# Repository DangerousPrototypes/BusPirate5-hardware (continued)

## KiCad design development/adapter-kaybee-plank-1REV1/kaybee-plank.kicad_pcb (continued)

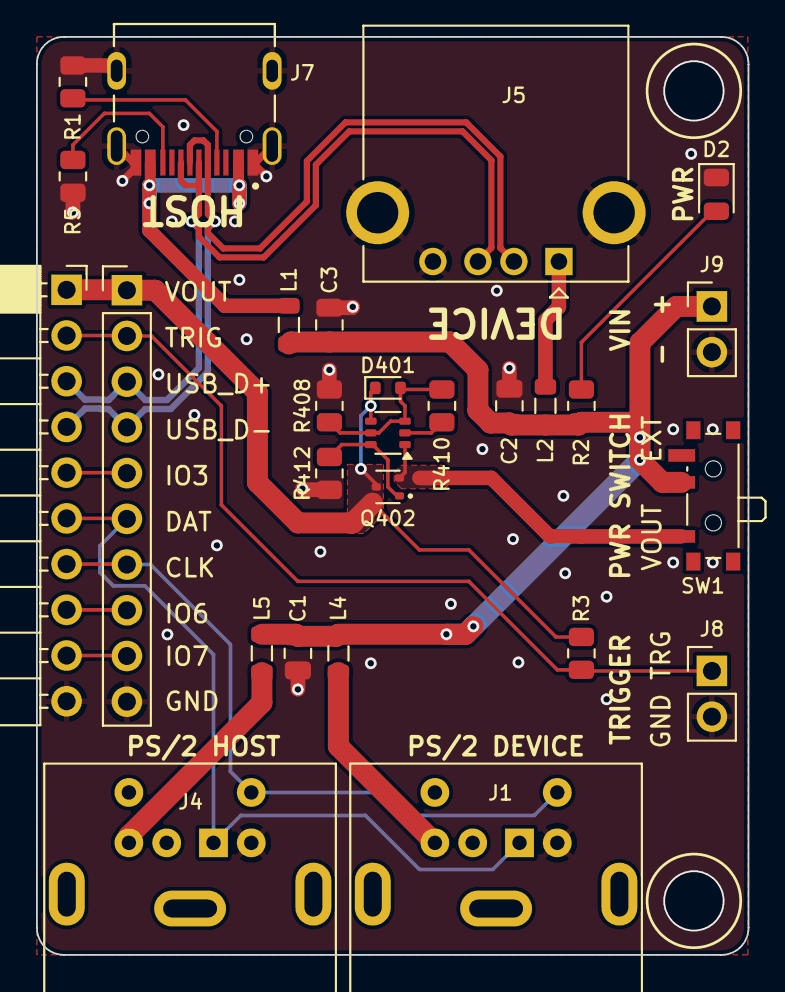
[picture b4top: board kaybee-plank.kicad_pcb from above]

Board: 2 copper layers, 39.5 x 51.0 mm, 27 parts (0 on the bottom side), 22 nets.

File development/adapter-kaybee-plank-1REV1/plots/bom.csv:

Item,Qty,Reference(s),Value,Footprint,szlcsc_partnum
1,3,"C1, C2, C3",47uF/CL21A226MAYNNNE,Capacitor_SMD:C_0805_2012Metric,C602037
2,1,D2,LED,LED_SMD:LED_0805_2012Metric,
3,1,D401,1N4148WT,Diode_SMD:D_SOD-523,C2828426
4,2,"J1, J4",Mini-DIN-6,connector-mini-din-6:Connector_Mini-DIN_Female_6Pin_2rows,C77848
5,1,J2,Conn_01x10,Connector_PinSocket_2.54mm:PinSocket_1x10_P2.54mm_Horizontal,
6,1,J5,USB_A,Connector_USB:USB_A_CONNFLY_DS1095-WNR0,C456018
7,1,J7,TYPE-C-31-M-12,TYPE-C-31-M-12:HRO_TYPE-C-31-M-12,C2858270
8,2,"J8, J9",Conn_01x02_Pin,Connector_PinHeader_2.54mm:PinHeader_1x02_P2.54mm_Vertical,C2905434
9,4,"L1, L2, L4, L5",CBW201209U300T,Inductor_SMD:L_0805_2012Metric,C139190
10,1,Q401,BCM857BS-7-F,Package_TO_SOT_SMD:SOT-363_SC-70-6,C105896
11,1,Q402,BC2301T 2.8A,Package_TO_SOT_SMD:SOT-523,C21714127
12,2,"R1, R5",5.1K,Resistor_SMD:R_0805_2012Metric,C27834
13,2,"R2, R3",2K,Resistor_SMD:R_0805_2012Metric,C2907315
14,1,R408,68K,Resistor_SMD:R_0805_2012Metric,C17801
15,1,R410,10K,Resistor_SMD:R_0805_2012Metric,C17414
16,1,R412,100K,Resistor_SMD:R_0805_2012Metric,C149504
17,1,SW1,SW_SPDT,Button_Switch_SMD:SW_SPDT_PCM12,C431540

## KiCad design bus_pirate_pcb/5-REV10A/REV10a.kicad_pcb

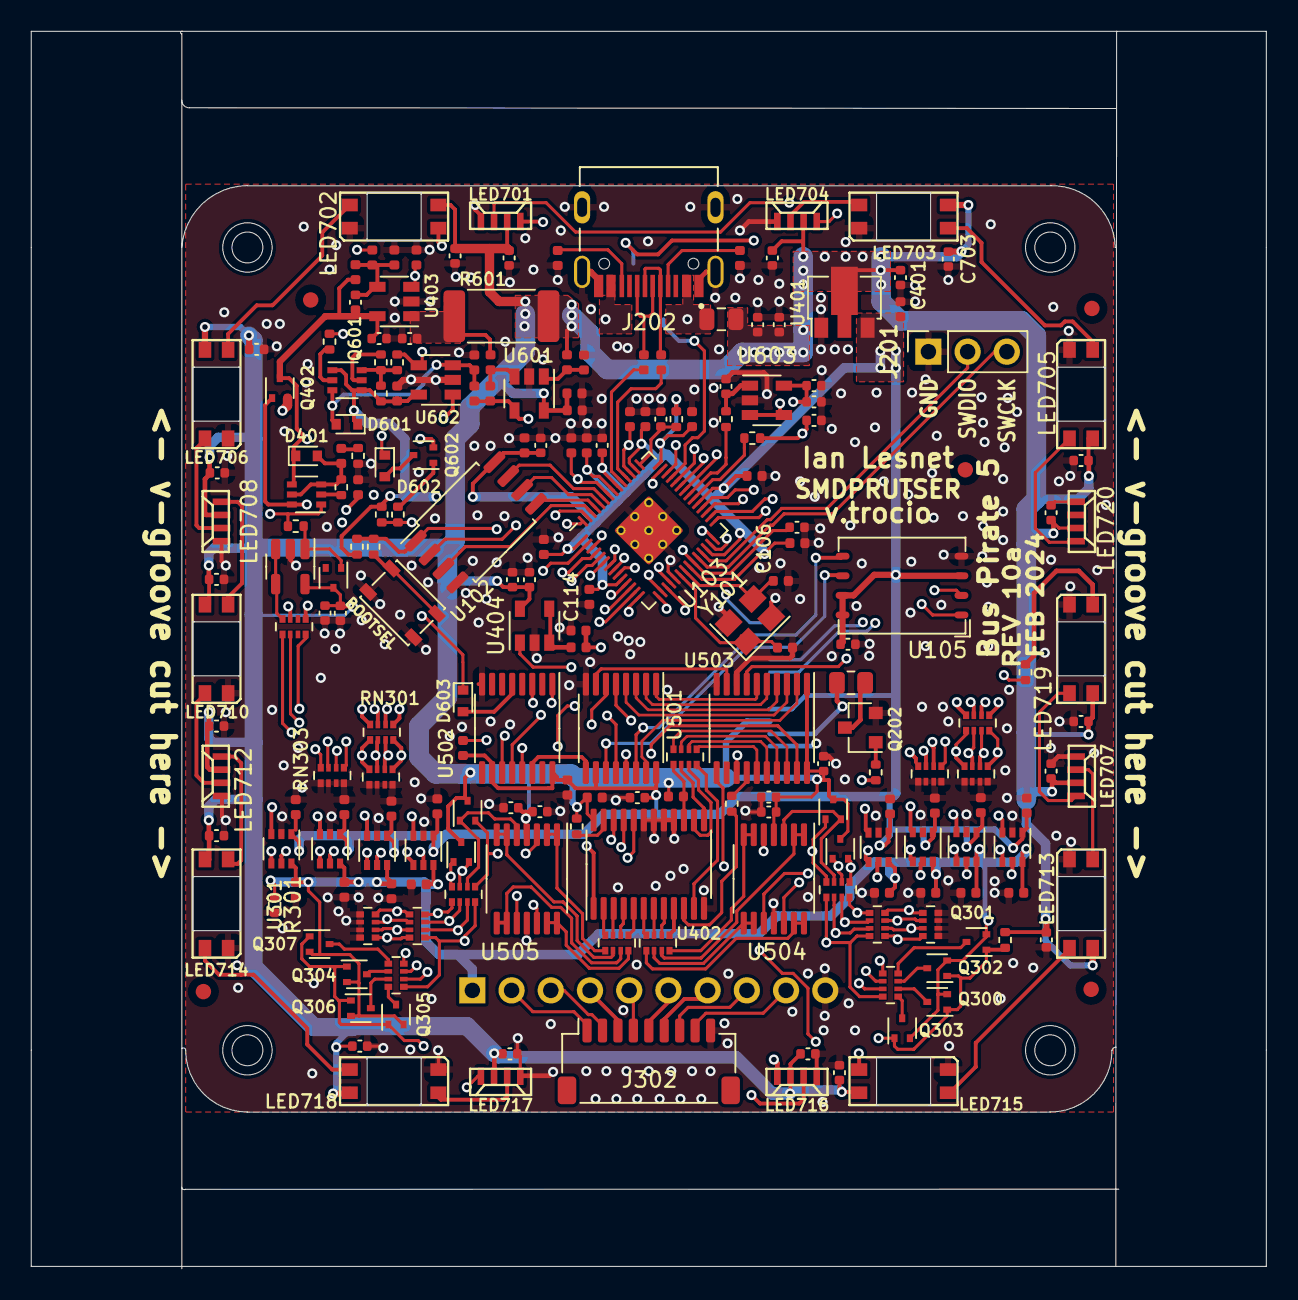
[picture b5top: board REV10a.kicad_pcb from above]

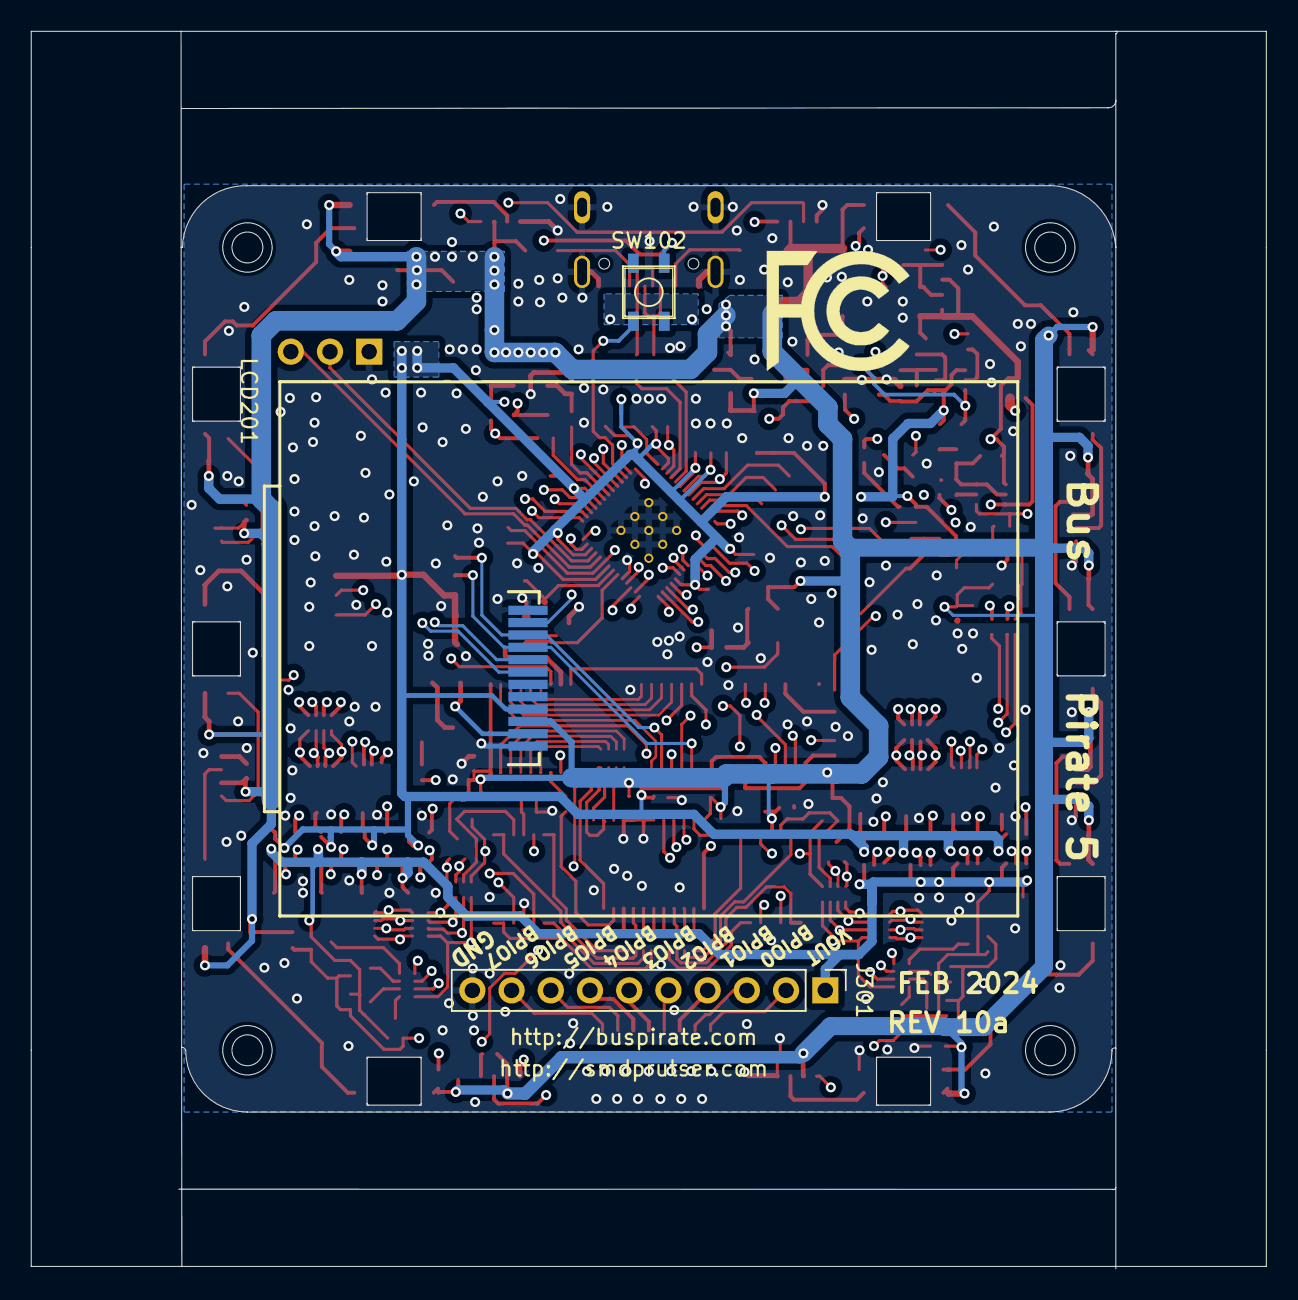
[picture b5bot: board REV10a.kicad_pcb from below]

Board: 4 copper layers, 80.0 x 80.0 mm, 220 parts (4 on the bottom side), 183 nets.

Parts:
C103, C110, C111, C112, C113, C114, C115, C116, C117, C118, C121, C301, C302, C303, C304, C305, C306, C307, C308, C309, C310, C311, C312, C313, C314, C315, C316, C403, C406, C414, C415, C416, C501, C502, C503, C506, C508, C510, C602, C605, C701, C702, C703, C704, C705, C706, C707, C708, C710, C712, C713, C714, C715, C716, C717, C718, C719, C720: 0.1uF; C_0402_1005Metric
C104, C107, C108, C109, C405, C413, C504, C507, C509, C601: 2.2uF; C_0402_1005Metric
C105, C106: 15pF; C_0402_1005Metric
C201, C202, C401, C402, C404, C407: 4.7uF; C_0402_1005Metric
C408: 120pF; C_0402_1005Metric
C603: DNF; C_0402_1005Metric
D401, D601, D602, D603: 1N4148WT; D_SOD-523
D500, D501, D502, D503, D504: BAS40T-05; SOT-523
FID1, FID2, FID3, FID4, FID5: Fiducial; Fiducial_1mm_Mask2mm
H1, H2, H3, H4: MountingHole; MountingHole_3.2mm_M3
J201: Conn_01x03; PinSocket_1x03_P2.54mm_Vertical
J202: TYPE-C-31-M-12; HRO_TYPE-C-31-M-12
J301: Conn_01x10; PinHeader_1x10_P2.54mm_Vertical
J302: Conn_01x09; JST_SH_SM09B-SRSS-TB_1x09-1MP_P1.00mm_Horizontal
L201: 1.5A; L_0805_2012Metric
LCD201: TFT_20_QT200H1201
LED701, LED704, LED707, LED708, LED712, LED716, LED717, LED720: SK6812-side-a_b
LED702, LED703, LED705, LED706, LED710, LED713, LED714, LED715, LED718, LED719: SK6812-mini-e
Q202: MMBT7002K; SOT-23
Q300, Q301, Q302, Q303, Q304, Q305, Q306, Q307, Q402, Q602: SI2301; SOT-523
Q401: BCM857; SOT-363_SC-70-6
Q601: MMDT3906; SOT-363_SC-70-6
R101, R502, R602, R603: 1K; R_0402_1005Metric
R102: DNF; R_0402_1005Metric
R103, R208, R608, R612: 200R; R_0402_1005Metric
R201, R204: 5.1K; R_0402_1005Metric
R202, R203: 22R; R_0402_1005Metric
R209: 33R; R_0805_2012Metric
R301, R313, R402, R406, R407, R410, R414, R415, R501, R606, R609, R610, R611, R613: 10K; R_0402_1005Metric
R316, R320: 510R; R_0402_1005Metric
R319, R401, R412: 100K; R_0402_1005Metric
R403: 102K; R_0402_1005Metric
R404: 133K; R_0402_1005Metric
R405, R408, R409, R604, R605: 33K; R_0402_1005Metric
R601: 0R2; R_2512_6332Metric_Pad1.40x3.35mm_HandSolder
RN301, RN305, RN306, RN309: 330R; R_Array_Convex_4x0402
RN302, RN304, RN307, RN310: 1M; R_Array_Convex_4x0402
RN303, RN308, RN317, RN318: 100K; R_Array_Convex_4x0402
RN311, RN312: 10K; R_Array_Convex_4x0402
RN315, RN400, RN401, RN402: 510R; R_Array_Convex_4x0402
SW101: SW_SPST; SW_SPST_PTS810
SW102: 4P_button_sw; GT-TC026X-HXXX-LX
U102: W25Q128JVSIQ; SOP-8_5.28x5.23mm_P1.27mm
U103: RP2040; RP2040-QFN-56
U105: MT29F1G01ABAFDWB; U-PDFN-8
U301, U302, U303, U304, U305, U306, U307, U308: AiP74LVC1T45GC363.TR; SOT-363_SC-70-6
U401: ME6211A33PG-N; SOT-89-3
U402: CD4067; TSSOP-24_4.4x7.8mm_P0.65mm
U403: AP2127; SOT-23-5
U404, U506, U603: LMV321; SOT-23-5
U501, U502: AIP74HC595TA; TSSOP-16_4.4x5mm_P0.65mm
U503: AIP74HCT245TA; TSSOP-20_4.4x6.5mm_P0.65mm
U504, U505: LMV324; TSSOP-14_4.4x5mm_P0.65mm
U601: LMV321A; SOT-23-5
U602: LMV331; SOT-23-5
Y101: 12Mhz; Crystal_SMD_3225-4Pin_3.2x2.5mm
logo1: fcc_logo; logo_fcc

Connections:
+1V1: C107.1, C117.1, C118.1, U103.23 (DVDD), U103.45 (VREG_VOUT), U103.50 (DVDD)
+3V3: C103.1, C104.1, C108.2, C110.1, C111.1, C112.1, C113.1, C114.1, C115.1, C116.1, C121.1, C301.2, C302.2, C303.2, C307.2, C308.2, C309.2, C313.2, C314.2, C402.1, C413.1, C414.2, C501.2, C502.2, C605.1, D601.1 (K), LCD201.4 (VCC), Q601.1 (E1), Q601.4 (E2), R102.1, R103.1, R501.1, R609.1, R613.1, SW102.4, U102.8 (VCC), U103.1 (IOVDD), U103.10 (IOVDD), U103.22 (IOVDD), U103.26 (RUN), U103.33 (IOVDD), U103.42 (IOVDD), U103.44 (VREG_IN), U103.48 (USB_VDD), U103.49 (IOVDD), U105.3 (WP/IO2), U105.7 (HOLD/IO3), U105.8 (VCC), U301.1 (VCCA), U302.1 (VCCA), U303.1 (VCCA), U304.1 (VCCA), U305.1 (VCCA), U306.1 (VCCA), U307.1 (VCCA), U308.1 (VCCA), U401.3 (VOUT), U501.10 (~SRCLR), U501.16 (VCC), U502.10 (~SRCLR), U502.16 (VCC), U602.5 (V+), U603.5 (V+)
+VUSB: C201.2, C202.2, C401.1, C403.2, C405.2, C406.1, C503.2, C504.2, C506.1, C507.2, C508.2, C509.2, C510.2, C601.1, C602.2, C701.2, C702.2, C703.2, C704.2, C705.2, C706.2, C707.2, C708.2, C710.2, C712.2, C713.2, C714.2, C715.2, C716.2, C717.2, C718.2, C719.2, C720.2, D500.3, D501.3, D502.3, D503.3, D504.3, L201.1, LCD201.3 (LED-A), LED701.3 (VDD), LED702.1 (VDD), LED703.1 (VDD), LED704.3 (VDD), LED705.1 (VDD), LED706.1 (VDD), LED707.3 (VDD), LED708.3 (VDD), LED710.1 (VDD), LED712.3 (VDD), LED713.1 (VDD), LED714.1 (VDD), LED715.1 (VDD), LED716.3 (VDD), LED717.3 (VDD), LED718.1 (VDD), LED719.1 (VDD), LED720.3 (VDD), R313.2, R320.2, R402.1, R601.1, R602.2, U401.2 (VIN), U402.24 (VCC), U404.5 (V+), U503.1 (A->B), U503.20 (VCC), U504.4 (V+), U505.4 (V+), U506.5 (V+), U601.5 (V+)
AMUX_EN: R402.2, RN315.1 (R1.1), U402.15 (~E)
AMUX_OUT: R406.2, R407.2, U103.40 (GPIO28_ADC2)
AMUX_S0: R316.1, U402.10 (S0)
AMUX_S1: RN315.4 (R1.1), U402.11 (S1)
AMUX_S2: RN315.3 (R1.1), U402.14 (S2)
AMUX_S3: RN315.2 (R1.1), U402.13 (S3)
BPIO0: J301.2, J302.1, RN305.1 (R1.1), RN312.1 (R1.1), RN318.8 (R1.8)
BPIO1: J301.3, J302.2, RN305.2 (R1.1), RN312.2 (R1.1), RN318.7 (R1.8)
BPIO2: J301.4, J302.3, RN305.3 (R1.1), RN312.3 (R1.1), RN318.6 (R1.8)
BPIO3: J301.5, J302.4, RN305.4 (R1.1), RN312.4 (R1.1), RN318.5 (R1.8)
BPIO4: J301.6, J302.5, RN309.1 (R1.1), RN311.1 (R1.1), RN317.8 (R1.8)
BPIO5: J301.7, J302.6, RN309.2 (R1.1), RN311.2 (R1.1), RN317.7 (R1.8)
BPIO6: J301.8, J302.7, RN309.3 (R1.1), RN311.3 (R1.1), RN317.6 (R1.8)
BPIO7: J301.9, J302.8, RN309.4 (R1.1), RN311.4 (R1.1), RN317.5 (R1.8)
BUFDIR0: RN303.8 (R1.8), U103.2 (GPIO0), U301.5 (DIR)
BUFDIR1: RN303.7 (R1.8), U103.3 (GPIO1), U302.5 (DIR)
BUFDIR2: RN303.6 (R1.8), U103.4 (GPIO2), U303.5 (DIR)
BUFDIR3: RN303.5 (R1.8), U103.5 (GPIO3), U304.5 (DIR)
BUFDIR4: RN308.8 (R1.8), U103.6 (GPIO4), U305.5 (DIR)
BUFDIR5: RN308.7 (R1.8), U103.7 (GPIO5), U306.5 (DIR)
BUFDIR6: RN308.6 (R1.8), U103.8 (GPIO6), U307.5 (DIR)
BUFDIR7: RN308.5 (R1.8), U103.9 (GPIO7), U308.5 (DIR)
BUFIO0: RN301.8 (R1.8), U103.11 (GPIO8)
BUFIO1: RN301.7 (R1.8), U103.12 (GPIO9)
BUFIO2: RN301.6 (R1.8), U103.13 (GPIO10)
BUFIO3: RN301.5 (R1.8), U103.14 (GPIO11)
BUFIO4: RN306.8 (R1.8), U103.15 (GPIO12)
BUFIO5: RN306.7 (R1.8), U103.16 (GPIO13)
BUFIO6: RN306.6 (R1.8), U103.17 (GPIO14)
BUFIO7: RN306.5 (R1.8), U103.18 (GPIO15)
BUTTONS: SW102.1, U103.39 (GPIO27_ADC1)
CURRENT_ADJ_MCU: R415.2, U103.34 (GPIO22)
CURRENT_DETECT: Q602.2 (S), R610.2, RN402.5 (R1.8), U602.4
CURRENT_EN: R612.2, R613.2, U502.1 (QB)
CURRENT_EN_OVERRIDE: D603.2 (A), U502.5 (QF)
CURRENT_RESET: R611.1, U502.3 (QD)
CURRENT_SENSE: R605.1, R606.2, U103.41 (GPIO29_ADC3), U601.4
DISPLAY_BACKLIGHT: R208.1, U501.5 (QF)
DISPLAY_CS: LCD201.8 (CS), U103.37 (GPIO25)
DISPLAY_DP: LCD201.7 (WR/SPI_A0), U103.36 (GPIO24)
DISPLAY_LED-K: LCD201.2 (LED-K), R209.2
DISPLAY_RESET: LCD201.11 (RESET), U501.6 (QG)
GND: C103.2, C104.2, C105.2, C106.2, C107.2, C108.1, C109.2, C110.2, C111.2, C112.2, C113.2, C114.2, C115.2, C116.2, C117.2, C118.2, C121.2, C201.1, C202.1, C301.1, C302.1, C303.1, C304.2, C305.2, C306.2, C307.1, C308.1, C309.1, C310.2, C311.2, C312.2, C313.1, C314.1, C315.2, C316.2, C401.2, C402.2, C403.1, C404.2, C405.1, C406.2, C407.2, C413.2, C414.1, C415.1, C416.1, C501.1, C502.1, C503.1, C504.1, C506.2, C507.1, C508.1, C509.1, C510.1, C601.2, C602.1, C603.1, C605.2, C701.1, C702.1, C703.1, C704.1, C705.1, C706.1, C707.1, C708.1, C710.1, C712.1, C713.1, C714.1, C715.1, C716.1, C717.1, C718.1, C719.1, C720.1, J201.1, J202.A1B12 (GND), J202.B1A12 (GND), J202.S1 (SHIELD), J202.S2 (SHIELD), J202.S3 (SHIELD), J202.S4 (SHIELD), J301.10, J302.9, LCD201.1 (GND), LCD201.5 (GND), LCD201.6 (GND), LCD201.12 (GND), LED701.1 (VSS), LED702.3 (VSS), LED703.3 (VSS), LED704.1 (VSS), LED705.3 (VSS), LED706.3 (VSS), LED707.1 (VSS), LED708.1 (VSS), LED710.3 (VSS), LED712.1 (VSS), LED713.3 (VSS), LED714.3 (VSS), LED715.3 (VSS), LED716.1 (VSS), LED717.1 (VSS), LED718.3 (VSS), LED719.3 (VSS), LED720.1 (VSS), Q202.2 (S), R201.1, R204.1, R301.2, R401.2, R405.2, R407.1, R409.2, R412.2, R604.1, RN302.1 (R1.1), RN302.2 (R1.1), RN302.3 (R1.1), RN302.4 (R1.1), RN303.1 (R1.1), RN303.2 (R1.1), RN303.3 (R1.1), RN303.4 (R1.1), RN304.5 (R1.8), RN304.6 (R1.8), RN304.7 (R1.8), RN304.8 (R1.8), RN307.1 (R1.1), RN307.2 (R1.1), RN307.3 (R1.1), RN307.4 (R1.1), RN308.1 (R1.1), RN308.2 (R1.1), RN308.3 (R1.1), RN308.4 (R1.1), RN310.5 (R1.8), RN310.6 (R1.8), RN310.7 (R1.8), RN310.8 (R1.8), SW101.2 (B), U102.4 (VSS), U103.19 (TESTEN), U103.57 (GND), U105.4 (VSS), U301.2 (GND), U302.2 (GND), U303.2 (GND), U304.2 (GND), U305.2 (GND), U306.2 (GND), U307.2 (GND), U308.2 (GND), U401.1 (GND), U402.12 (GND), U402.16 (I15), U402.17 (I14), U402.18 (I13), U402.19 (I12), U403.2 (GND), U404.2 (V-), U501.8 (GND), U502.8 (GND), U503.8 (A6), U503.10 (GND), U504.11 (V-), U505.11 (V-), U506.2 (V-), U601.2 (V-), U602.2 (V-), U603.2 (V-), Y101.2, Y101.4
LEDS_CDO: R502.1, U503.13 (B5)
MUX_BPIO0: RN401.5 (R1.8), U505.1, U505.2 (-)
MUX_BPIO1: RN401.6 (R1.8), U505.6 (-), U505.7
MUX_BPIO2: RN401.7 (R1.8), U505.8, U505.9 (-)
MUX_BPIO3: RN401.8 (R1.8), U505.13 (-), U505.14
MUX_BPIO4: RN400.5 (R1.8), U504.13 (-), U504.14
MUX_BPIO5: RN400.6 (R1.8), U504.8, U504.9 (-)
MUX_BPIO6: RN400.7 (R1.8), U504.1, U504.2 (-)
MUX_BPIO7: RN400.8 (R1.8), U504.6 (-), U504.7
MUX_VREF_VOUT: RN402.8 (R1.8), U506.3 (-), U506.4
unnamed: D401.2 (A), Q401.3 (C2), Q401.5 (B2), R408.2, R410.2
unnamed: C603.2, D601.2 (A), Q601.3 (C2), R606.1, U602.3 (-)
unnamed: D602.2 (A), Q602.3 (D)
unnamed: J202.A5 (CC1), R201.2
unnamed: J202.B5 (CC2), R204.2
unnamed: J202.A4B9 (VBUS), J202.B4A9 (VBUS), L201.2
unnamed: LED701.4 (DI), LED702.2 (DO)
unnamed: LED701.2 (DO), LED704.4 (DI)
unnamed: LED702.4 (DI), LED706.2 (DO)
unnamed: LED703.4 (DI), LED704.2 (DO)
unnamed: LED703.2 (DO), LED705.4 (DI)
unnamed: LED705.2 (DO), LED720.4 (DI)
unnamed: LED706.4 (DI), LED708.2 (DO)
unnamed: LED707.4 (DI), LED719.2 (DO)
unnamed: LED707.2 (DO), LED713.4 (DI)
unnamed: LED708.4 (DI), LED710.2 (DO)
unnamed: LED710.4 (DI), LED712.2 (DO)
unnamed: LED712.4 (DI), LED714.2 (DO)
unnamed: LED713.2 (DO), LED715.4 (DI)
unnamed: LED714.4 (DI), LED718.2 (DO)
unnamed: LED715.2 (DO), LED716.4 (DI)
unnamed: LED716.2 (DO), LED717.4 (DI)
unnamed: LED717.2 (DO), LED718.4 (DI)
unnamed: LED719.4 (DI), R502.2
unnamed: Q202.3 (D), R209.1
unnamed: Q202.1 (G), R208.2
unnamed: Q300.3 (D), RN311.6 (R1.8)
unnamed: Q301.3 (D), RN311.8 (R1.8)
unnamed: Q302.3 (D), RN311.7 (R1.8)
unnamed: Q303.3 (D), RN311.5 (R1.8)
unnamed: Q304.3 (D), RN312.6 (R1.8)
unnamed: Q305.3 (D), RN312.8 (R1.8)
unnamed: Q306.3 (D), RN312.7 (R1.8)
unnamed: Q307.3 (D), RN312.5 (R1.8)
unnamed: Q401.2 (B1), R410.1
unnamed: Q401.6 (C1), Q402.1 (G), R412.1
unnamed: Q601.2 (B1), R611.2
unnamed: Q601.6 (C1), R608.2, R609.2, R610.1
unnamed: Q601.5 (B2), R608.1
unnamed: Q602.1 (G), R612.1
unnamed: R408.1, R409.1
unnamed: RN301.1 (R1.1), RN302.8 (R1.8), U301.3 (A)
unnamed: RN301.2 (R1.1), RN302.7 (R1.8), U302.3 (A)
unnamed: RN301.3 (R1.1), RN302.6 (R1.8), U303.3 (A)
unnamed: RN301.4 (R1.1), RN302.5 (R1.8), U304.3 (A)
unnamed: RN304.1 (R1.1), RN305.8 (R1.8), U301.4 (B)
unnamed: RN304.2 (R1.1), RN305.7 (R1.8), U302.4 (B)
unnamed: RN304.3 (R1.1), RN305.6 (R1.8), U303.4 (B)
unnamed: RN304.4 (R1.1), RN305.5 (R1.8), U304.4 (B)
unnamed: RN306.1 (R1.1), RN307.8 (R1.8), U305.3 (A)
unnamed: RN306.2 (R1.1), RN307.7 (R1.8), U306.3 (A)
unnamed: RN306.3 (R1.1), RN307.6 (R1.8), U307.3 (A)
unnamed: RN306.4 (R1.1), RN307.5 (R1.8), U308.3 (A)
unnamed: RN309.8 (R1.8), RN310.1 (R1.1), U305.4 (B)
unnamed: RN309.7 (R1.8), RN310.2 (R1.1), U306.4 (B)
unnamed: RN309.6 (R1.8), RN310.3 (R1.1), U307.4 (B)
unnamed: RN309.5 (R1.8), RN310.4 (R1.1), U308.4 (B)
unnamed: RN315.8 (R1.8), U503.18 (B0)
unnamed: RN315.7 (R1.8), U503.17 (B1)
unnamed: RN315.6 (R1.8), U503.16 (B2)
unnamed: RN315.5 (R1.8), U503.15 (B3)
unnamed: D502.2, RN317.1 (R1.1), U504.12 (+)
unnamed: D502.1, RN317.2 (R1.1), U504.10 (+)
unnamed: D501.2, RN317.3 (R1.1), U504.3 (+)
unnamed: D501.1, RN317.4 (R1.1), U504.5 (+)
unnamed: D504.2, RN318.1 (R1.1), U505.3 (+)
unnamed: D504.1, RN318.2 (R1.1), U505.5 (+)
unnamed: D503.2, RN318.3 (R1.1), U505.10 (+)
unnamed: D503.1, RN318.4 (R1.1), U505.12 (+)
unnamed: RN400.1 (R1.1), U402.9 (I0)
unnamed: RN400.2 (R1.1), U402.8 (I1)
unnamed: RN400.3 (R1.1), U402.7 (I2)
unnamed: RN400.4 (R1.1), U402.6 (I3)
unnamed: RN401.1 (R1.1), U402.5 (I4)
unnamed: RN401.2 (R1.1), U402.4 (I5)
unnamed: RN401.3 (R1.1), U402.3 (I6)
unnamed: RN401.4 (R1.1), U402.2 (I7)
unnamed: RN402.1 (R1.1), U402.20 (I11)
unnamed: RN402.2 (R1.1), U402.21 (I10)
unnamed: RN402.4 (R1.1), U402.22 (I9)
unnamed: R101.2, SW101.1 (A)
unnamed: C109.1, R103.2, U103.43 (ADC_AVDD)
unnamed: C105.1, U103.20 (XIN), Y101.1
unnamed: C106.1, U103.21 (XOUT), Y101.3
unnamed: U402.1 (COM), U404.1 (+)
unnamed: R320.1, U402.23 (I8)
unnamed: C408.2, R403.2, R404.2, R405.1, U403.4 (ADJ)
unnamed: R406.1, U404.3 (-), U404.4
unnamed: U501.15 (QA), U503.2 (A0)
unnamed: U501.1 (QB), U503.6 (A4)
unnamed: U501.2 (QC), U503.5 (A3)
unnamed: U501.3 (QD), U503.4 (A2)
unnamed: U501.4 (QE), U503.3 (A1)
unnamed: U501.9 (QH'), U502.14 (SER)
unnamed: U501.7 (QH), U503.9 (A7)
unnamed: R316.2, U503.14 (B4)
unnamed: D500.1, R319.1, U506.1 (+)
unnamed: R602.1, R604.2, U601.1 (+)
unnamed: R603.1, R605.2, U601.3 (-)
unnamed: C416.2, R415.1, U602.1 (+)
unnamed: C415.2, R414.1, U603.1 (+)
PULLUP_EN: Q300.1 (G), Q301.1 (G), Q302.1 (G), Q303.1 (G), Q304.1 (G), Q305.1 (G), Q306.1 (G), Q307.1 (G), R313.1, U503.11 (B7)
QSPI_SCLK: U102.6 (CLK), U103.52 (QSPI_SCLK)
QSPI_SD0: U102.5 (DI), U103.53 (QSPI_SD0)
QSPI_SD1: U102.2 (DO), U103.55 (QSPI_SD1)
QSPI_SD2: U102.3 (WP), U103.54 (QSPI_SD2)
QSPI_SD3: U102.7 (HOLD), U103.51 (QSPI_SD3)
QSPI_SS: R101.1, R102.2, U102.1 (CS), U103.56 (QSPI_SS)
RGB_CDO: U103.28 (GPIO17), U503.7 (A5)
SD_CS: U103.38 (GPIO26_ADC0), U105.1 (CS)
SHIFT_EN: R501.2, U103.32 (GPIO21), U501.13 (~OE), U502.13 (~OE), U503.19 (CE)
SHIFT_LATCH: U103.31 (GPIO20), U501.12 (RCLK), U502.12 (RCLK)
SPI_CDI: U103.27 (GPIO16), U105.2 (SO/IO1)
SPI_CDO: LCD201.10 (SPI_SDA), U103.30 (GPIO19), U105.5 (SI/IO0), U501.14 (SER)
SPI_CLK: LCD201.9 (RS/SPI_SCL), U103.29 (GPIO18), U105.6 (SCK), U501.11 (SRCLK), U502.11 (SRCLK)
SWCLK: J201.3, U103.24 (SWCLK)
SWDIO: J201.2, U103.25 (SWD)
USB_D+: R203.1, U103.47 (USB_DP)
USB_D-: R202.1, U103.46 (USB_DM)
USB_N: J202.A7 (DN1), J202.B7 (DN2), R202.2
USB_P: J202.A6 (DP1), J202.B6 (DP2), R203.2
VREF_VOUT: C304.1, C305.1, C306.1, C310.1, C311.1, C312.1, C315.1, C316.1, J301.1, Q300.2 (S), Q301.2 (S), Q302.2 (S), Q303.2 (S), Q304.2 (S), Q305.2 (S), Q306.2 (S), Q307.2 (S), Q401.1 (E1), Q402.2 (S), R301.1, R319.2, U301.6 (VCCB), U302.6 (VCCB), U303.6 (VCCB), U304.6 (VCCB), U305.6 (VCCB), U306.6 (VCCB), U307.6 (VCCB), U308.6 (VCCB)
VREG_ADJ: R403.1, U603.3 (-), U603.4
VREG_ADJ_MCU: R414.2, U103.35 (GPIO23)
VREG_EN: D602.1 (K), D603.1 (K), R401.1, U403.3 (SHUTDOWN)
VREG_OUT: C407.1, C408.1, D401.1 (K), Q401.4 (E2), Q402.3 (D), R404.1, RN402.7 (R1.8), U403.5 (OUT)
VREG_VIN: C404.1, R601.2, R603.2, U403.1 (VIN)

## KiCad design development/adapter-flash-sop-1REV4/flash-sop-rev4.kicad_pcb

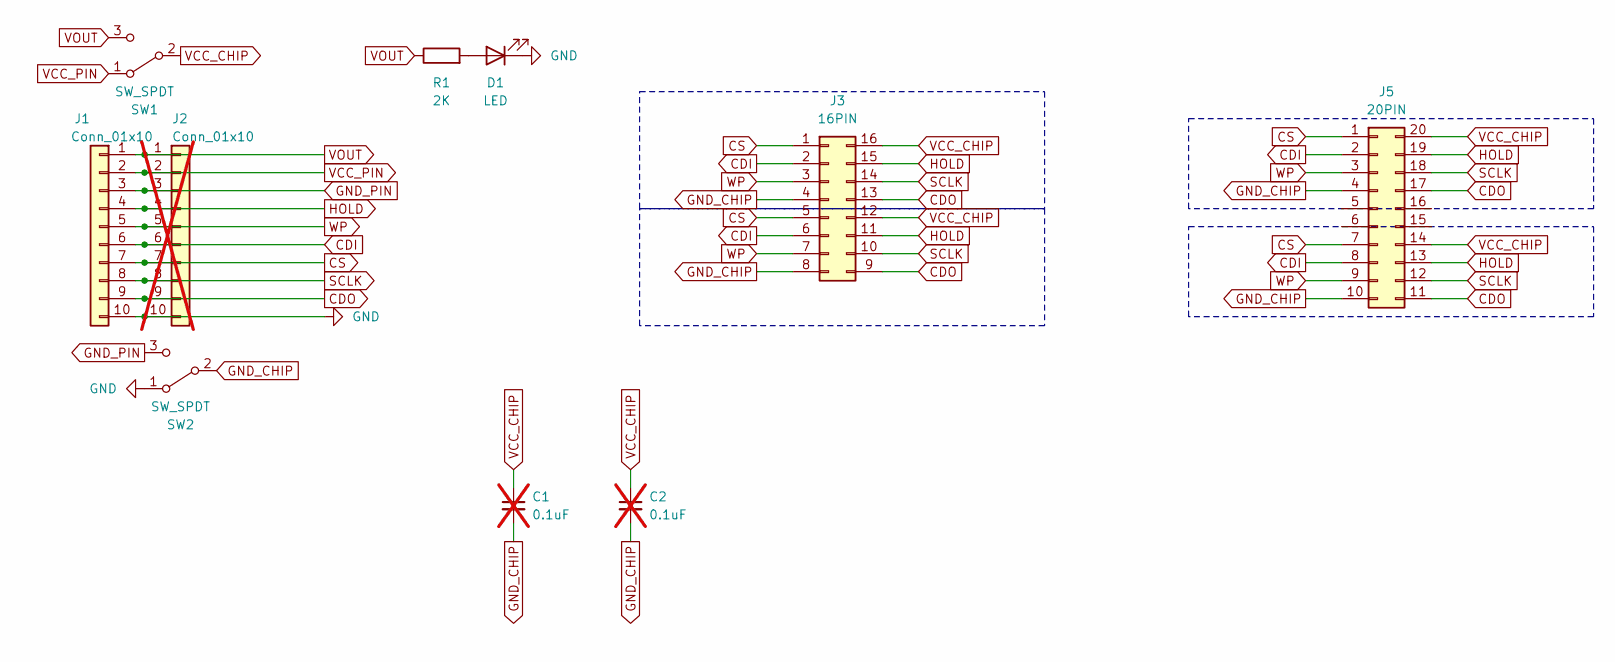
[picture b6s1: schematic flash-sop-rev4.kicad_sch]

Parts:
C1, C2: 0.1uF; C_0805_2012Metric; not fitted
D1: LED; LED_0805_2012Metric
J1: Conn_01x10; PinSocket_1x10_P2.54mm_Horizontal
J2: Conn_01x10; PinHeader_1x10_P2.54mm_Vertical; not fitted
J3: 16PIN; 16PIN_SCOKET
J5: 20PIN; 20PIN_SCOKET
R1: 2K; R_0805_2012Metric
SW1, SW2: SW_SPDT; SW_SPDT_PCM12

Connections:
CDI: J1.6, J2.6, J3.2, J3.6, J5.2, J5.8
CDO: J1.9, J2.9, J3.9, J3.13, J5.11, J5.17
CS: J1.7, J2.7, J3.1, J3.5, J5.1, J5.7
GND: D1.1 (K), J1.10, J2.10, SW2.1 (A)
GND_CHIP: C1.2, C2.2, J3.4, J3.8, J5.4, J5.10, SW2.2 (B)
GND_PIN: J1.3, J2.3, SW2.3 (C)
HOLD: J1.4, J2.4, J3.11, J3.15, J5.13, J5.19
unnamed: D1.2 (A), R1.2
SCLK: J1.8, J2.8, J3.10, J3.14, J5.12, J5.18
VCC_CHIP: C1.1, C2.1, J3.12, J3.16, J5.14, J5.20, SW1.2 (B)
VCC_PIN: J1.2, J2.2, SW1.1 (A)
VOUT: J1.1, J2.1, R1.1, SW1.3 (C)
WP: J1.5, J2.5, J3.3, J3.7, J5.3, J5.9

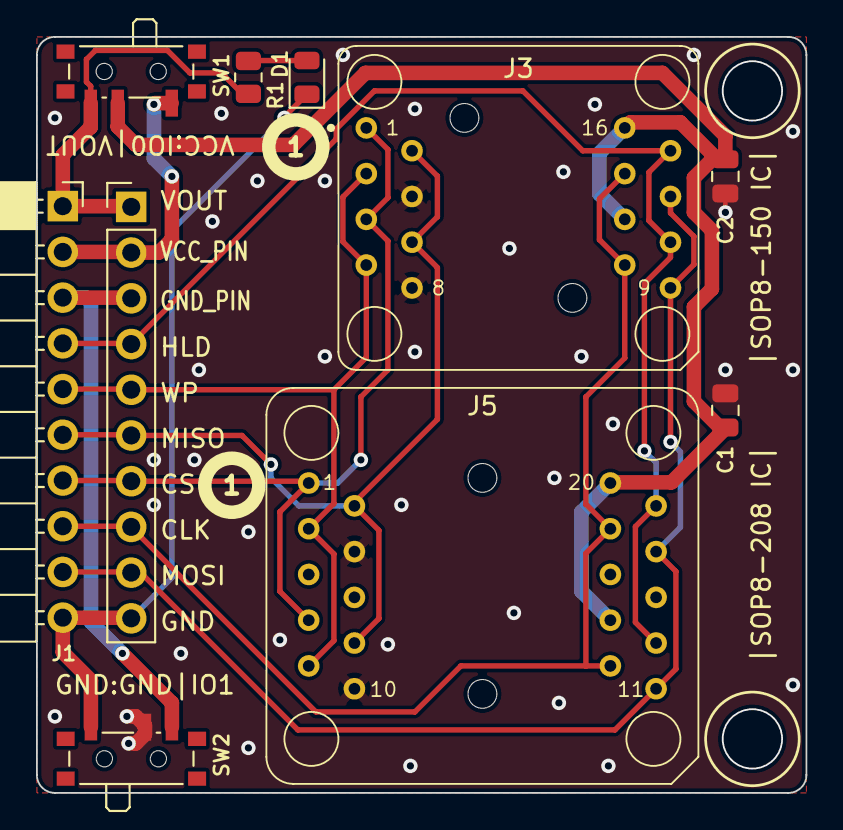
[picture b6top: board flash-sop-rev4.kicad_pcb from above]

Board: 2 copper layers, 42.8 x 42.0 mm, 10 parts (0 on the bottom side), 13 nets.

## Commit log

2023-09-21 Bus Pirate 5 hardware initial check in
2023-11-26 Bus Pirate REV10. KF141r/v boards.
2023-11-28 KF141 adapters REV2 - tighter spacing.
2023-11-30 Add pulldown on VREF. Change VUSB MUX series resistor to 510R. May be other value updates that didn't get checked in previously.
2023-12-01 silkscreen art
2023-12-02 REV10: add missing LED, fix LED placement.
2023-12-04 silkscreen labels
2024-01-15 enclosure plug
2024-01-17 ignore kicad temp
2024-01-17 git ignore
2024-01-17 rev10 pcb
2024-01-17 Raspberry Pi PICO header silkscreen
2024-01-17 schematic cleanup
2024-01-17 remove pdf
2024-02-17 milled pins
2024-02-22 KF011C breakout board
2024-02-22 REV10 correct PCB. Renamed 10a for clarity.
2024-02-22 mvoe kf011c up one folder
2024-02-22 wago quick connect cleanup
2024-02-22 kf141 update files and ignore
2024-02-22 kf011c move to correct folder
2024-02-22 rev10(a) gitignore
2024-04-04 readme
2024-04-04 license
2024-04-25 remove beta smartcard board
2024-04-25 add DIP, SOP, WSON SPI flash adapter boards
2024-04-25 rename zif to dip
2024-07-11 SOP8 SPI Flash socket LOTES version
2024-08-08 Bus Pirate 5XL
2024-08-08 Bus Pirate 6
2024-10-15 PCB updates discussion
2024-10-16 remove old pullups, remove 1M pull-down. Add footprints and updated PCB.
2024-10-17 partial move to dfn/qfn
2024-10-20 Update enclosure kicad files - remove "mask" from diff to work with recent OpenSCAD and BOSLII
2024-10-20 minor updates to collaborative board redesign
2024-11-01 BP7REV0A
2024-11-05 BP7 REV1
2024-11-05 BP7 REV1 missing files
2024-11-12 Add VOUT protection from electronic_eel: https://forum.buspirate.com/t/port-protection-for-rev7/712/37 . Minor cleanup of top page.
2024-11-12 Move CURRENT_DETECT back to AMUX
2024-11-20 Blank Plank prototyping board with proto pattern from http://git.io/vNUDX CC-BY-4.0
2025-01-14 IR Toy
2025-01-14 vpp maker
2025-01-14 rs232 adapter
2025-01-14 sim IC card adapter
2025-02-18 change to 27R usb termination resistors as recommended by RasPi (7-REV1)
2025-02-18 change to 27R usb termination resistors as recommended by RasPi (7-rev0a)
2025-02-18 update aux voltage creation
    - 100pF/200k RC oscillator for reduced current consumption
    - set footprints to 0402, use default symbols that are used in other parts of the schematics
    - use 4.7µF / 0402 cap for -5V:
    I guess we can get by with this as we don't have that much bias, so the cap loss should be ok
    - use 10µF / 0805 for 9V:
    Too high voltage for a smaller part, voltage biassing would kill nearly all capacitance
2025-02-18 adapt protection for the AP2127 voltage regulator
    - add a PMEG2020EJ for backflow-handling
    - remove the previous backflow protection circuit
    - remove the AP2127+circuit from the "VOUT protection" sheet, it was redundant
2025-02-18 reduce BOM lines by changing the Vaux oscillator to 120pF || 180k
2025-02-18 adapt the IO-port protection
    - move to the bpu-iobuffer sheet, remove duplicate on VOUT-protection
    - use SP3002-04JTG in SOT363 instead of the larger IP4220CZ6F
    - add datasheet, resistor wattage to part fields
2025-02-18 add ESD protection for the USB port too
2025-02-18 change the decoupling caps for the SP3002-04JTG TVS diodes to 4.7µF
    Lower impedanced decoupling, can absorb more energy fast
2025-02-18 adapt VOUT protection as tested
2025-02-18 replace MMBT7002K in SOT-23 with 2N7002T in SOT-523
2025-02-18 replace one more MMBT7002K in SOT-23 with 2N7002T in SOT-523 (display led backlight)
2025-02-18 replace 10µF / 0402 cap with 4.7µF / 0402 to save one BOM line
    - new reset / bootloader circuit
    - adjust resistor to 560k
    - exact values have to be tested (cap varies by mfg due to voltage derating)
2025-02-18 add DFN1010D-3 / SOT1215 footprint for PMXB56EN mosfets
2025-02-19 TCA6416ARTWR IO expander, 2.2uF->4.7uF
2025-02-19 BP7 REV 0a: 2.2uF, 4.7uF -> 10uF/6.3V CL05A106MQ5NUN
2025-02-19 BP7REV1 2.2uF, 4.7uF-> 10uF/6.3V CL05A106MQ5NUN. 520K->470K on reset/bootloader switch.
2025-02-19 remove gate series resistor for the display backlight - it is unnecessary
2025-02-19 specify part numbers and manufacturers in more detail - 10µF / 0805 caps - 2N7002KT fets
2025-02-19 use a 1N4148WT instead of BAS40-04 in the VOUT protection
    - used to pull low the aux voltage when the external voltage is lower than -5V
    - SOD-523 is smaller than SOT-523
    - The BAS40-04 was easier blown in ESD/surge tests.
    Placement solved this, but the 1N4148WT will be more resilient
    - The increased forward voltage shouldn't matter, we must just go low enough to not turn on the FETs
2025-02-19 improve TCA6416ARTWR schematics - connect exposed pad to GND - mark unused INT pin as such
2025-02-19 improve decoupling for the memory ICs (NOR, NAND, PSRAM) - do not use 100nF 0402 || 10µF 0402 - just use 10µF 0402 - the lowest impedance and resonance freq is mostly determined by size - so the 100n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
2025-02-19 move LCD background LED current limiting resistor from cathode to anode
    - there were several soldering defects on the LCD connector observed during manufacturing
    - often the LEDs were shorted to ground
    - this modification will protect the LEDs and the traces in this case, making rework easier
2025-02-19 change resistor naming from k to K to unify BOM lines
    change the gate pullup resistor from 20k to 18k to remove one BOM line
2025-02-19 mark some more unconnected pins as such
    LM358 DFN from ST: "the exposed pad can be left floating or connected to GND" -> leave it floating as it is now
2025-02-22 PSRAM pullup to 10K
2025-02-22 remove excess 510R series resistors on 4067
2025-02-22 TPC5120 symbol
2025-02-23 BP7REV1-prototype candidate #1
2025-02-24 Remove DNF footprints, locate PWM pins for power supply adjustment. Change PWM op-amp to DFN and buffer also the CURRENT_ADJ. Remove a FET gate resistor from current limiter.
2025-02-24 Remove VREG bypass diode. Fix XL9555 I2C address
2025-02-24 cleanup microcontroller schematic
2025-02-25 Change XL9555 I2C address to advance from TCA6416ARTWR. Change adjustable voltage regulator to correct part number.
2025-02-26 Final I2C and PWM pin selection.
2025-02-26 remvoe 1n4148 from current fuse
2025-02-26 Show that XL9555 is not connected.
2025-03-26 7R1 PCB routed
2025-03-27 7REV1B in .zip archive
2025-03-27 add feedback cap
2025-03-27 add feedback caps
2025-04-15 kaybee sniffer plank
2025-04-15 add szlcsc part numbers
2025-04-25 3d models on BP 6 pcb
2025-04-25 ddr5 hacking board
2025-05-17 Bus Pirate enclosure v2 STL files
2025-06-16 reorg, but forgot to check changes first :(
2025-06-16 Reorganization of hardware repo. In development and unreleased boards moved to "development" folder. Cleanup and rename Bus Pirate PCB versions.
2025-06-17 kaybee production package
2025-06-17 vout protection test
2025-06-18 Change pinout on I2C quick connect
2025-06-18 BP 7R2 VOUT protection
2025-06-18 kaybee plank - change pull-up resistor supply source
2025-07-04 7R2 with vout protection
2025-07-05 7R2a and b
2025-11-04 move quick I2C and ddr5 out of the dev folder
